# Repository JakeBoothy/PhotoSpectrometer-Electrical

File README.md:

# PhotoSpectrometer-Electrical
PCB Design for my visible photospectrometer.

## Version 1

Version 1 was completed for a class project. It performed reasonably well but had a mistake and left out some much needed features. The files are here for reference but it is not recommended that you build it.

## Version 2

I am working on version 2 right now. There is more info on my website but I am cleaning up the design and adding some more features.

* Peltier drivers
* Better amplifier design
* Change microcontroller to STM32
* TFT Screen and encoder
* External ADC
* SD Card
* And much more!

Additionally I am going to do a full optical design with raytracing software and a full mechanical redesign. 

Design was done in eagle.

More info on my blog

https://jakehasahobby.wordpress.com/2017/12/03/electrical-design/
https://jakehasahobby.wordpress.com/2018/07/18/plan-new-features/

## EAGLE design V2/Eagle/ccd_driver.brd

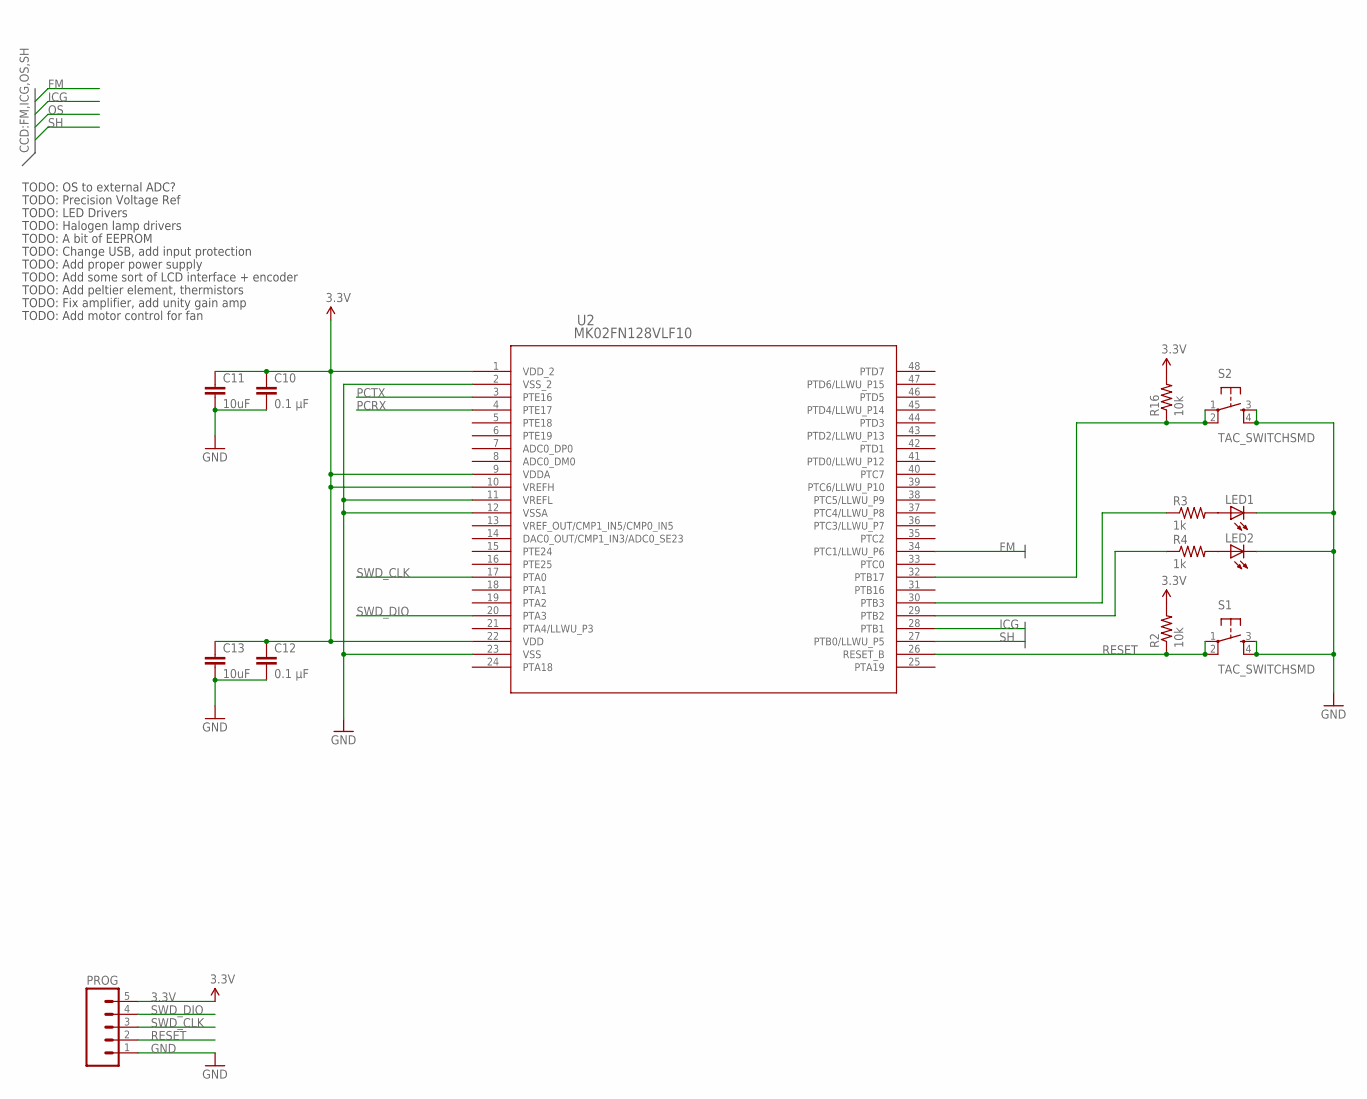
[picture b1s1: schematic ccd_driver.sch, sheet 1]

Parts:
C10, C12: 0.1 µF; C1206
C11, C13: 10uF; C1206
LED1, LED2: LEDCHIPLED_0805; CHIPLED_0805
PROG: M05LOCK; 1X05_LOCK
R2, R16: 10k; R0805
R3, R4: 1k; R0805
S1, S2: TAC_SWITCHSMD; TACTILE-SWITCH-SMD
U2: MK02FN128VLF10; LQFP-48_7X7X1.6

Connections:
3.3V: C10.1, C11.1, C12.1, C13.1, PROG.5, R2.2, R16.2, U2.1 (VDD_2), U2.9 (VDDA), U2.10 (VREFH), U2.22 (VDD); also elsewhere on the board
FM: U2.34 (PTC1/LLWU_P6); also elsewhere on the board
GND: C10.2, C11.2, C12.2, C13.2, LED1.C, LED2.C, PROG.1, S1.3, S1.4, S2.3, S2.4, U2.2 (VSS_2), U2.11 (VREFL), U2.12 (VSSA), U2.23 (VSS); also elsewhere on the board
ICG: U2.28 (PTB1); also elsewhere on the board
unnamed: R16.1, S2.1, S2.2, U2.32 (PTB17)
unnamed: R3.1, U2.30 (PTB3)
unnamed: LED1.A, R3.2
unnamed: LED2.A, R4.2
unnamed: R4.1, U2.29 (PTB2)
PCRX: U2.4 (PTE17); also elsewhere on the board
PCTX: U2.3 (PTE16); also elsewhere on the board
RESET: PROG.2, R2.1, S1.1, S1.2, U2.26 (RESET_B)
SH: U2.27 (PTB0/LLWU_P5); also elsewhere on the board
SWD_CLK: PROG.3, U2.17 (PTA0)
SWD_DIO: PROG.4, U2.20 (PTA3)

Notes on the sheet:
TODO: OS to external ADC?
TODO: Precision Voltage Ref
TODO: LED Drivers
TODO: Halogen lamp drivers
TODO: A bit of EEPROM
TODO: Change USB, add input protection
TODO: Add proper power supply
TODO: Add some sort of LCD interface + encoder
TODO: Add peltier element, thermistors
TODO: Fix amplifier, add unity gain amp
TODO: Add motor control for fan

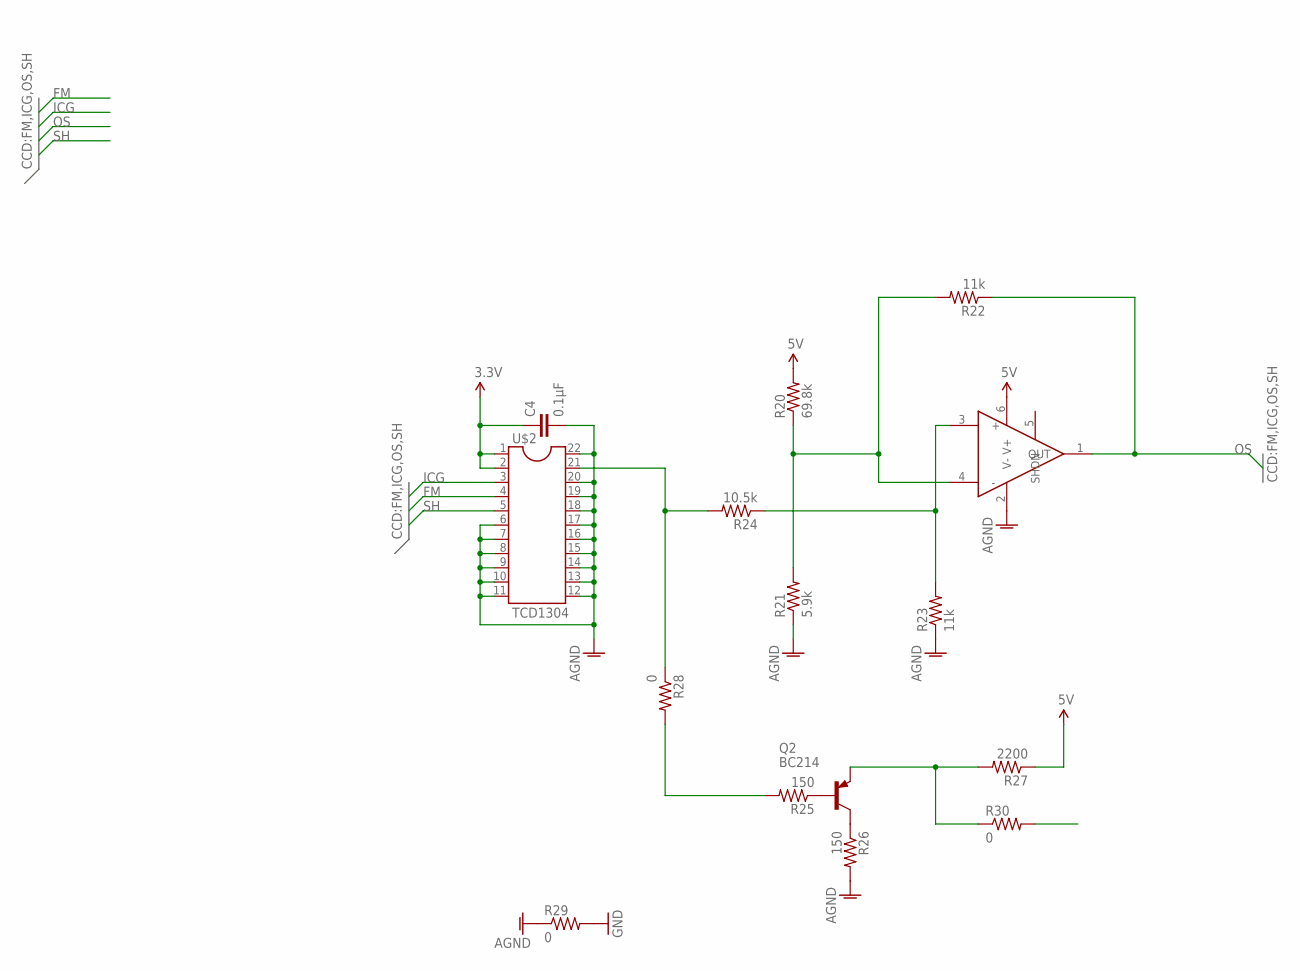
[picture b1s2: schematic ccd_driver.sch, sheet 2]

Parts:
C4: 0.1µF; C1206
Q2: BC214; TO92
R20: 69.8k; R0805
R21: 5.9k; R0805
R22, R23: 11k; R0805
R24: 10.5k; R0805
R25, R26: 150; R0805
R27: 2200; R0805
R28, R29, R30: 0; R0805
U$2: TCD1304
U$5: LTC6252; TSOT23-6

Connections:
3.3V: C4.1, U$2.1, U$2.2; also elsewhere on the board
5V: R20.2, R27.1, U$5.6 (V+); also elsewhere on the board
AGND: C4.2, R21.1, R23.1, R26.2, R29.1, U$2.6, U$2.7, U$2.8, U$2.9, U$2.10, U$2.11, U$2.12, U$2.13, U$2.14, U$2.15, U$2.16, U$2.17, U$2.18, U$2.19, U$2.20, U$2.22, U$5.2 (V-)
BU1: Q2.1 (E), R27.2, R30.1
FM: U$2.4; also elsewhere on the board
GND: R29.2; also elsewhere on the board
ICG: U$2.3; also elsewhere on the board
unnamed: R20.1, R21.2, R22.2, U$5.4 (-)
unnamed: R23.2, R24.1, U$5.3 (+)
unnamed: R24.2, R28.1, U$2.21
unnamed: Q2.2 (B), R25.1
unnamed: Q2.3 (C), R26.1
unnamed: R25.2, R28.2
OS: R22.1, R30.2, U$5.1 (OUT)
SH: U$2.5; also elsewhere on the board

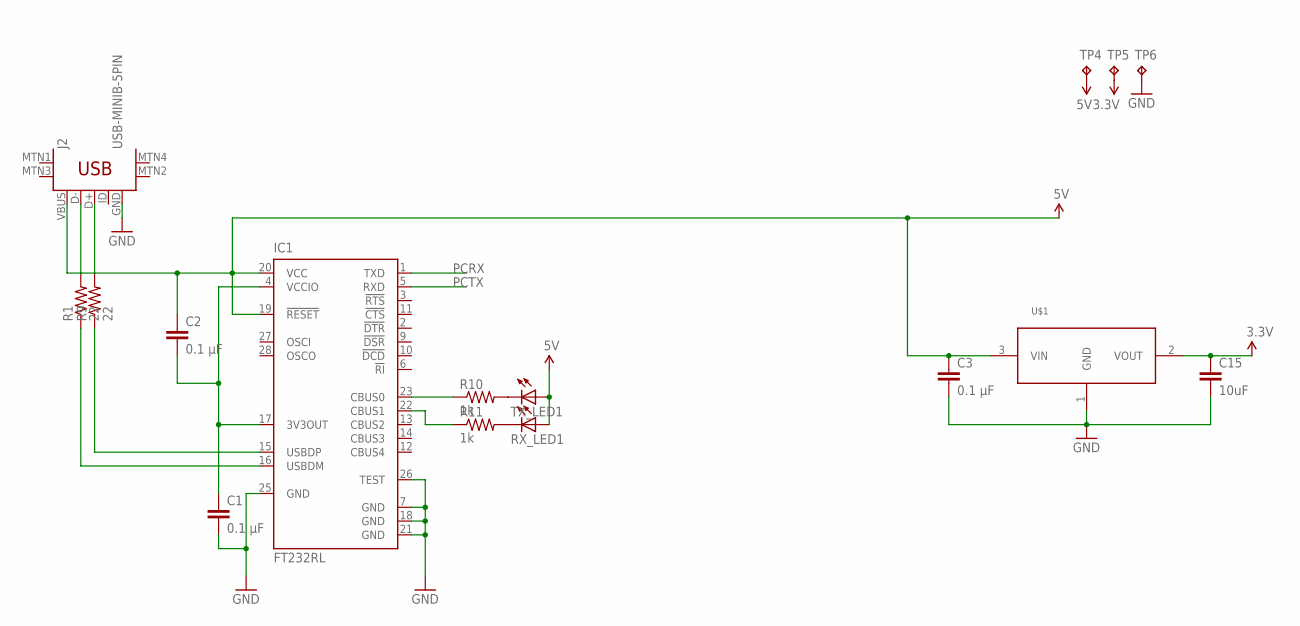
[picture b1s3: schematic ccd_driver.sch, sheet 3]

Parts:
C1, C2, C3: 0.1 µF; C1206
C15: 10uF; C1206
IC1: FT232RL; SSOP28
J2: USB-MINIB-5PIN; USB-MINIB
R1, R9: 22; R0805
R10, R11: 1k; R0805
RX_LED1: LEDCHIPLED_0805; CHIPLED_0805
TP4, TP5, TP6: TPPAD1-17Y; P1-17Y
TX_LED1: LEDCHIPLED_0805; CHIPLED_0805
U$1: LD1117V33; TO220H

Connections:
3.3V: C15.1, TP5.TP, U$1.2 (VOUT); also elsewhere on the board
5V: C2.1, C3.1, IC1.19 (!RESET), IC1.20 (VCC), J2.VBUS, RX_LED1.A, TP4.TP, TX_LED1.A, U$1.3 (VIN); also elsewhere on the board
GND: C1.2, C3.2, C15.2, IC1.7 (GND), IC1.18 (GND), IC1.21 (GND), IC1.25 (GND), IC1.26 (TEST), J2.GND, TP6.TP, U$1.1 (GND); also elsewhere on the board
unnamed: IC1.16 (USBDM), R1.1
unnamed: IC1.15 (USBDP), R9.1
unnamed: J2.D-, R1.2
unnamed: J2.D+, R9.2
unnamed: C1.1, C2.2, IC1.4 (VCCIO), IC1.17 (3V3OUT)
unnamed: IC1.23 (CBUS0), R10.1
unnamed: IC1.22 (CBUS1), R11.1
unnamed: R11.2, RX_LED1.C
unnamed: R10.2, TX_LED1.C
PCRX: IC1.1 (TXD); also elsewhere on the board
PCTX: IC1.5 (RXD); also elsewhere on the board

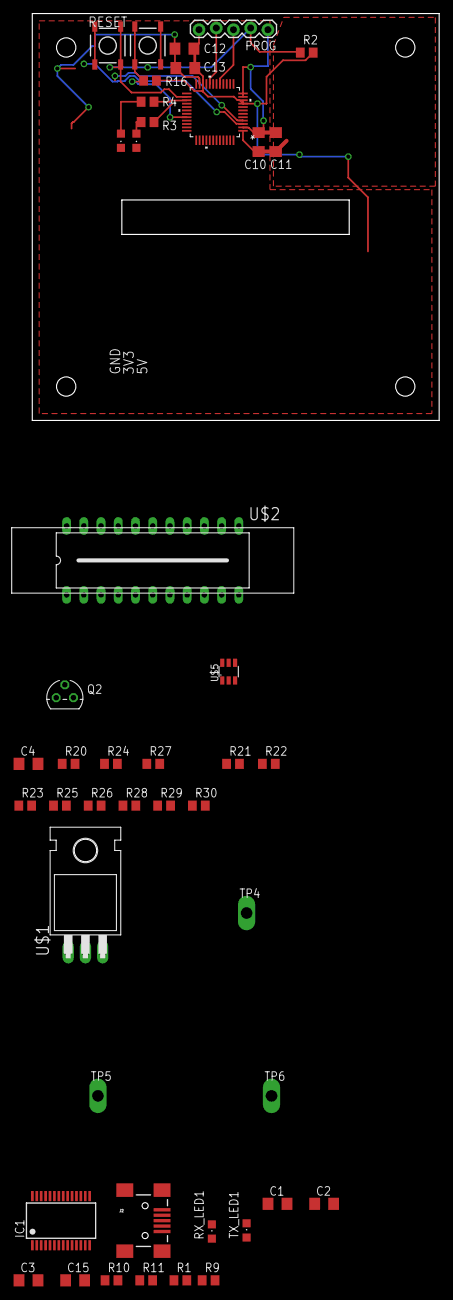
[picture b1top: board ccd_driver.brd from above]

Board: 2 copper layers, 60.0 x 60.0 mm, 45 parts (0 on the bottom side), 34 nets.

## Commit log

2018-01-04 init commit
2018-07-13 Added new version, v1 and v2
2018-07-13 Changed fM,SH,ICG pins to match with timers, added TODO list, cleaned up schematics and add them to different sheets
2018-07-13 added micro sd card
2018-07-18 added peltier driver: MOSFET w/ LPF, 12V 5A
2018-07-18 added LTSpice sch for pelt driver
2018-07-18 added 36V tolerant buck reg -> 3.3V 3A
2018-07-19 added fan mosfet control
2018-07-19 added different USB controller, micro usb, input protection
2018-07-19 removed old .brd file
2018-07-19 added thermistors
2018-07-19 changed jst fan connector
2018-07-21 added TFT screen + encoder, small cleanup, doubled peltier driver
2018-07-21 added my name to sch
2018-07-21 minor cleanup
2018-07-21 fixed readme
2018-07-21 added link to readme
2018-07-25 added precision voltage reference
2018-07-28 added current sense circuit for peltier drivers
2018-07-28 added notes on current sense
2018-07-28 added voltage sense, current sense might be useless
2018-07-28 minor changes
2018-07-28 changed most caps and resistors to 0603
2018-07-28 fixed fan circuit
2018-07-28 removed current sense because its not very smart
2018-07-28 added external ADC, need to finish circuit
2018-09-03 overhauled power subsection. Changed LC values for lpfs. Minor changes, added sim for output
2018-10-20 modified power supply again. Added filter, ldo, and charge pump for analog rails. Created new schematic frame. General organization and minor changes
2018-10-20 made matlab script to autocalculate amplifier resistor values
2018-10-20 added new amp circuit for CCD
2018-10-21 added filtering to analog section

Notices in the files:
parts and their libraries:
SparkFun-Aesthetics: Licensing: Creative Commons ShareAlike 4.0 International - https://creativecommons.org/licenses/by-sa/4.0
